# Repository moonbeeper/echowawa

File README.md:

# echowawa

> [!NOTE]
> This project is still in progress and not even close to being finished. Not even built yet.

Your typical DAC with bluetooth audio (with possible upgrades to use WiFi sources) and a USB C as an AUX port. It can output to either RCA jacks or a headphone jack. It also features a pretty fancy oled screen with its cool menu navigated via the knob.

The reason I made this was because of the fact that I am no longer a fan of using cheap bluetooth magic boxes with bad audio output when I can make my own magic box with probably better audio quality and a better design.

## Images

> The echowawa pcb

> The echowawa case

> The echowawa root schematic

> The echowawa power schematic

> The echowawa audio schematic

## BOM

> NOTE: This is a copy of the BOM.csv file. The shipping cost might be actually higher than the price listed here.

| Item | Quantity | LCSC Part Number | Cost EUR | Cost USD | Link |
|---|---|---|---|---|---|
| 1uF Capacitor | 26 | C29936 | 0,25 € | $0,28 | <https://lcsc.com/product-detail/Multilayer-Ceramic-Capacitors-MLCC-SMD-SMT_Samsung-Electro-Mechanics-CL10B105KA8NNNC_C29936.html> |
| 100nF Capacitor | 5 | C14663 | 0,22 € | $0,25 | <https://lcsc.com/product-detail/Multilayer-Ceramic-Capacitors-MLCC-SMD-SMT_YAGEO-CC0603KRX7R9BB104_C14663.html> |
| 10uF Electrolytic Capacitor | 4 | C22387953 | 0,21 € | $0,24 | <https://lcsc.com/product-detail/Aluminum-Electrolytic-Capacitors-SMD_FOLLON-EFVH025ADA100M0454_C22387953.html> |
| 2.2nF Capacitor | 4 | C107082 | 0,23 € | $0,26 | <https://lcsc.com/product-detail/Multilayer-Ceramic-Capacitors-MLCC-SMD-SMT_YAGEO-CC0603KRX7R9BB222_C107082.html> |
| 4.7uF Capacitor | 2 | C389010 | 0,30 € | $0,35 | <https://lcsc.com/product-detail/Multilayer-Ceramic-Capacitors-MLCC-SMD-SMT_muRata-GRM188Z71C475KE21D_C389010.html> |
| 27pF Capacitor | 2 | C376778 | 0,23 € | $0,26 | <https://lcsc.com/product-detail/Multilayer-Ceramic-Capacitors-MLCC-SMD-SMT_CCTC-TCC0603COG270J500CT_C376778.html> |
| 2.2uF Capacitor | 2 | C914769 | 0,43 € | $0,49 | <https://lcsc.com/product-detail/Multilayer-Ceramic-Capacitors-MLCC-SMD-SMT_YAGEO-CC0603KRX7R7BB225_C914769.html> |
| 100pF Capacitor | 2 | C14858 | 0,29 € | $0,33 | <https://lcsc.com/product-detail/Multilayer-Ceramic-Capacitors-MLCC-SMD-SMT_Samsung-Electro-Mechanics-CL10C101JB8NNNC_C14858.html> |
| 100uF Electrolytic Capacitor | 2 | C99837 | 0,28 € | $0,32 | <https://lcsc.com/product-detail/Aluminum-Electrolytic-Capacitors-SMD_ROQANG-RVE1V101M0607_C99837.html> |
| 3.3uF Capacitor | 1 | C5360803 | 0,55 € | $0,63 | <https://lcsc.com/product-detail/Multilayer-Ceramic-Capacitors-MLCC-SMD-SMT_CCTC-TCC0603X5R335M250CT_C5360803.html> |
| 5.1K Resistor | 4 | C105580 | 0,11 € | $0,12 | <https://lcsc.com/product-detail/Chip-Resistor-Surface-Mount_YAGEO-RC0603FR-075K1L_C105580.html> |
| 24K Resistor | 4 | C23352 | 0,10 € | $0,11 | <https://lcsc.com/product-detail/Chip-Resistor-Surface-Mount_UNI-ROYAL-0603WAF2402T5E_C23352.html> |
| 3.3K Resistor | 4 | C108078 | 0,11 € | $0,12 | <https://lcsc.com/product-detail/Chip-Resistor-Surface-Mount_YAGEO-RC0603FR-073K3L_C108078.html> |
| 4.7K Resistor | 3 | C99782 | 0,10 € | $0,11 | <https://lcsc.com/product-detail/Chip-Resistor-Surface-Mount_YAGEO-RC0603FR-074K7L_C99782.html> |
| 470 Resistor | 3 | C114669 | 0,11 € | $0,12 | <https://lcsc.com/product-detail/Chip-Resistor-Surface-Mount_YAGEO-RC0603FR-07470RL_C114669.html> |
| 0 Resistor | 1 | C95177  | 0,10 € | $0,11 | <https://lcsc.com/product-detail/Chip-Resistor-Surface-Mount_YAGEO-RC0603JR-070RL_C95177.html> |
| 10K Resistor | 1 | C98220 | 0,10 € | $0,11 | <https://lcsc.com/product-detail/Chip-Resistor-Surface-Mount_YAGEO-RC0603FR-0710KL_C98220.html> |
| 1.5K Resistor | 1 | C114668 | 0,11 € | $0,12 | <https://lcsc.com/product-detail/Chip-Resistor-Surface-Mount_YAGEO-RC0603FR-071K5L_C114668.html> |
| 1M Resistor | 1 | C105578 | 0,11 € | $0,12 | <https://lcsc.com/product-detail/Chip-Resistor-Surface-Mount_YAGEO-RC0603FR-071ML_C105578.html> |
| 100 Resistor | 1 | C105588 | 0,09 € | $0,10 | <https://lcsc.com/product-detail/Chip-Resistor-Surface-Mount_YAGEO-RC0603FR-07100RL_C105588.html> |
| 6.8uH Power Inductor | 1 | C135295 | 0,41 € | $0,47 | <https://lcsc.com/product-detail/Power-Inductors_SXN-Shun-Xiang-Nuo-Elec-SMNR6020-6R8MT_C135295.html> |
| Neopixel | 2 | C965555 | 0,36 € | $0,41 | <https://lcsc.com/product-detail/RGB-LEDs-Built-in-IC_Worldsemi-WS2812B-2020_C965555.html> |
| LED (Green) | 1 | C965804 | 0,39 € | $0,44 | <https://lcsc.com/product-detail/LED-Indication-Discrete_XINGLIGHT-XL-1608UGC-04_C965804.html> |
| XC6220B331MR | 2 | C86534 | 0,78 € | $0,89 | <https://lcsc.com/product-detail/Voltage-Regulators-Linear-Low-Drop-Out-LDO-Regulators_TOREX-XC6220B331MR-G_C86534.html> |
| TS5A22364DGSR | 2 | C105181 | 1,22 € | $1,40 | <https://lcsc.com/product-detail/Analog-Switches-Multiplexers_TI-TS5A22364DGSR_C105181.html> |
| ESP32-WROOM-32E-N8 | 1 | C701342 | 4,05 € | $4,65 | <https://lcsc.com/product-detail/WiFi-Modules_ESPRESSIF-ESP32-WROOM-32E-N8_C701342.html> |
| TLP185xSE | 1 | C7240 | 0,44 € | $0,51 | <https://lcsc.com/product-detail/Transistor-Photovoltaic-Output-Optoisolators_TOSHIBA-TLP185-GB-TPL-SE-T_C7240.html> |
| ADUM3160 | 1 | C284149 | 4,22 € | $4,85 | <https://lcsc.com/product-detail/Isolated-USB-ICs_ADI-ADUM3160BRWZ-RL_C284149.html> |
| F0505S-3WR2  | 1 | C5369564 | 1,93 € | $2,22 | <https://lcsc.com/product-detail/Isolated-Power-Modules_YLPTEC-F0505S-3WR2_C5369564.html> |
| PCM5100APWR | 1 | C131154 | 0,74 € | $0,85 | <https://lcsc.com/product-detail/ADCs-DACs-Special-Purpose_TI-PCM5100APWR_C131154.html> |
| PCM2912APJTR | 1 | C475497 | 3,80 € | $4,36 | <https://lcsc.com/product-detail/Audio-Interface-ICs_TI-PCM2912APJTR_C475497.html> |
| 6MHz Crystal | 1 | C7528811 | 0,39 € | $0,45 | <https://lcsc.com/product-detail/Crystals_YXC-Crystal-Oscillators-H6OEL89CSC-SUGYLC-6M_C7528811.html> |
| EC11E18244AU | 1 | C202365 | 1,71 € | $1,96 | <https://lcsc.com/product-detail/Rotary-Encoders_ALPSALPINE-EC11E18244AU_C202365.html> |
| Round TINY SMD Button | 2 | C720477 | 0,36 € | $0,41 | <https://lcsc.com/product-detail/Tactile-Switches_XUNPU-TS-1088-AR02016_C720477.html> |
| Audio Transformer | 2 | C596483 | 1,56 € | $1,79 | <https://lcsc.com/product-detail/Audio-Transformers_Sumida-ESMIT-4180-C_C596483.html> |
| RCA Jack | 2 | C18080 | 0,48 € | $0,55 | <https://lcsc.com/product-detail/RCA-Connector_BOOMELE-Boom-Precision-Elec-AV-5_C18080.html> |
| USBC Power Only | 1 | C668623 | 0,31 € | $0,35 | <https://lcsc.com/product-detail/USB-Connectors_SHOU-HAN-TYPE-C-6P-073_C668623.html> |
| USBC USB2.0 | 1 | C2988369 | 0,35 € | $0,40 | <https://lcsc.com/product-detail/USB-Connectors_G-Switch-GT-USB-7010ASV_C2988369.html> |
| Headphone Jack | 1 | C381131 | 0,46 € | $0,53 | <https://lcsc.com/product-detail/Audio-Connectors_XKB-Connection-PJ-3136-B_C381131.html> |
| 1.3 Inch OLED 128x64 | 1 | ----- | 2,80 € | $3,29 | <https://es.aliexpress.com/item/1005007451015054.html> |
| JLCPCB Echowawa 4 Layer PCB | 5 | ----- | 5,95 € | $7,00 | ----- |
| M2.5 Heat Inserts OD4mm Length 6mm  | 4 | ----- | 2,38 € | $2,79 | <https://es.aliexpress.com/item/1005003582355741.html> |
| M2.5 Allen Bolts 20mm Stainless Steel | 4 | ----- | 2,41 € | $2,83 | <https://es.aliexpress.com/item/32810872544.html> |
| USB to Serial Adapter | 1 |  | 1,41 € | $1,66 | <https://es.aliexpress.com/item/1005006445462581.html> |
| ~Shipping | ----- | ----- | 15 € | $17,61 | ----- |
| TOTAL | ----- | ----- | 57,94 € | $67,22 | ----- |

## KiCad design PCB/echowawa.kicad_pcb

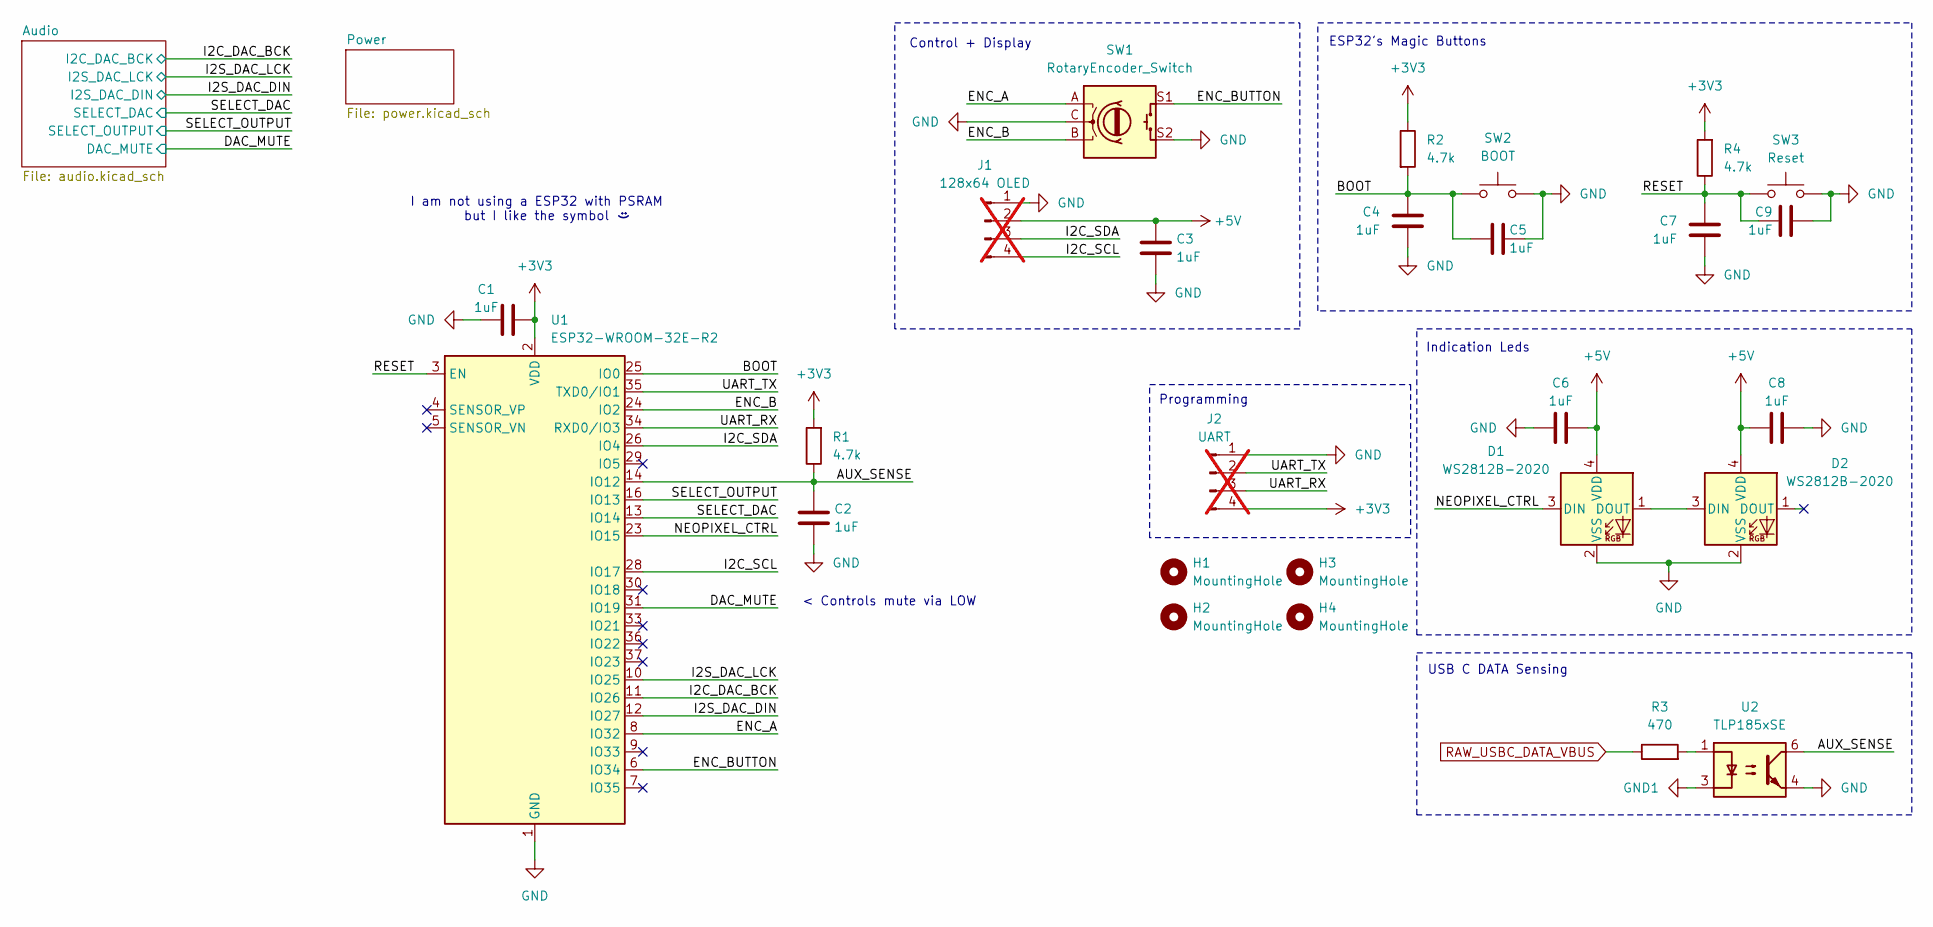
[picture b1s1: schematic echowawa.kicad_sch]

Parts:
C1, C2, C3, C4, C5, C6, C7, C8, C9: 1uF; C_0603_1608Metric_Pad1.08x0.95mm_HandSolder; LCSC C29936
D1, D2: WS2812B-2020; LED_WS2812B-2020_PLCC4_2.0x2.0mm; LCSC C965555
H1, H2, H3, H4: MountingHole; MountingHole_2.7mm_M2.5
J1: 128x64 OLED; PinHeader_1x04_P2.54mm_Vertical; not fitted
J2: UART; PinHeader_1x04_P2.54mm_Vertical; not fitted
R1, R2, R4: 4.7k; R_0603_1608Metric_Pad0.98x0.95mm_HandSolder; LCSC C99782
R3: 470; R_0603_1608Metric_Pad0.98x0.95mm_HandSolder; LCSC C114669
SW1: RotaryEncoder_Switch; RotaryEncoder_Alps_EC11E-Switch_Vertical_H20mm; LCSC C202365
SW2: BOOT; SW-SMD_L3.9-W3.0-P4.45; LCSC C720477
SW3: Reset; SW-SMD_L3.9-W3.0-P4.45; LCSC C720477
U1: ESP32-WROOM-32E-R2; ESP32-WROOM-32D; LCSC C701342
U2: TLP185xSE; SOIC-4_4.55x3.7mm_P2.54mm; LCSC C7240

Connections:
+3V3: C1.1, J2.4, R1.2, R2.1, R4.2, U1.2 (VDD); also elsewhere on the board
+5V: C3.2, C6.2, C8.1, D1.4 (VDD), D2.4 (VDD), J1.2; also elsewhere on the board
/AUX_SENSE: C2.2, R1.1, U1.14 (IO12), U2.6
/BOOT: C4.2, C5.1, R2.2, SW2.1, U1.25 (IO0); also elsewhere on the board
/DAC_MUTE: U1.31 (IO19); also elsewhere on the board
/ENC_A: SW1.A, U1.8 (IO32)
/ENC_B: SW1.B, U1.24 (IO2)
/ENC_BUTTON: SW1.S1, U1.6 (IO34)
/I2C_DAC_BCK: U1.11 (IO26); also elsewhere on the board
/I2C_SCL: J1.4, U1.28 (IO17)
/I2C_SDA: J1.3, U1.26 (IO4)
/I2S_DAC_DIN: U1.12 (IO27); also elsewhere on the board
/I2S_DAC_LCK: U1.10 (IO25); also elsewhere on the board
/NEOPIXEL_CTRL: D1.3 (DIN), U1.23 (IO15)
/RESET: C7.2, C9.1, R4.1, SW3.1, U1.3 (EN); also elsewhere on the board
/SELECT_DAC: U1.13 (IO14); also elsewhere on the board
/SELECT_OUTPUT: U1.16 (IO13); also elsewhere on the board
/UART_RX: J2.3, U1.34 (RXD0/IO3)
/UART_TX: J2.2, U1.35 (TXD0/IO1)
GND: C1.2, C2.1, C3.1, C4.1, C5.2, C6.1, C7.1, C8.2, C9.2, D1.2 (VSS), D2.2 (VSS), J1.1, J2.1, SW1.C, SW1.S2, SW2.2, SW3.2, U1.1 (GND), U1.15 (GND), U1.38 (GND), U1.39 (GND), U2.4; also elsewhere on the board
GND1: U2.3; also elsewhere on the board
unnamed: D1.1 (DOUT), D2.3 (DIN)
unnamed: R3.2, U2.1
RAW_USBC_DATA_VBUS: R3.1; also elsewhere on the board

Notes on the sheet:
ESP32's Magic Buttons
Programming
Indication Leds
< Controls mute via LOW
USB C DATA Sensing
Control + Display
I am not using a ESP32 with PSRAM but I like the symbol

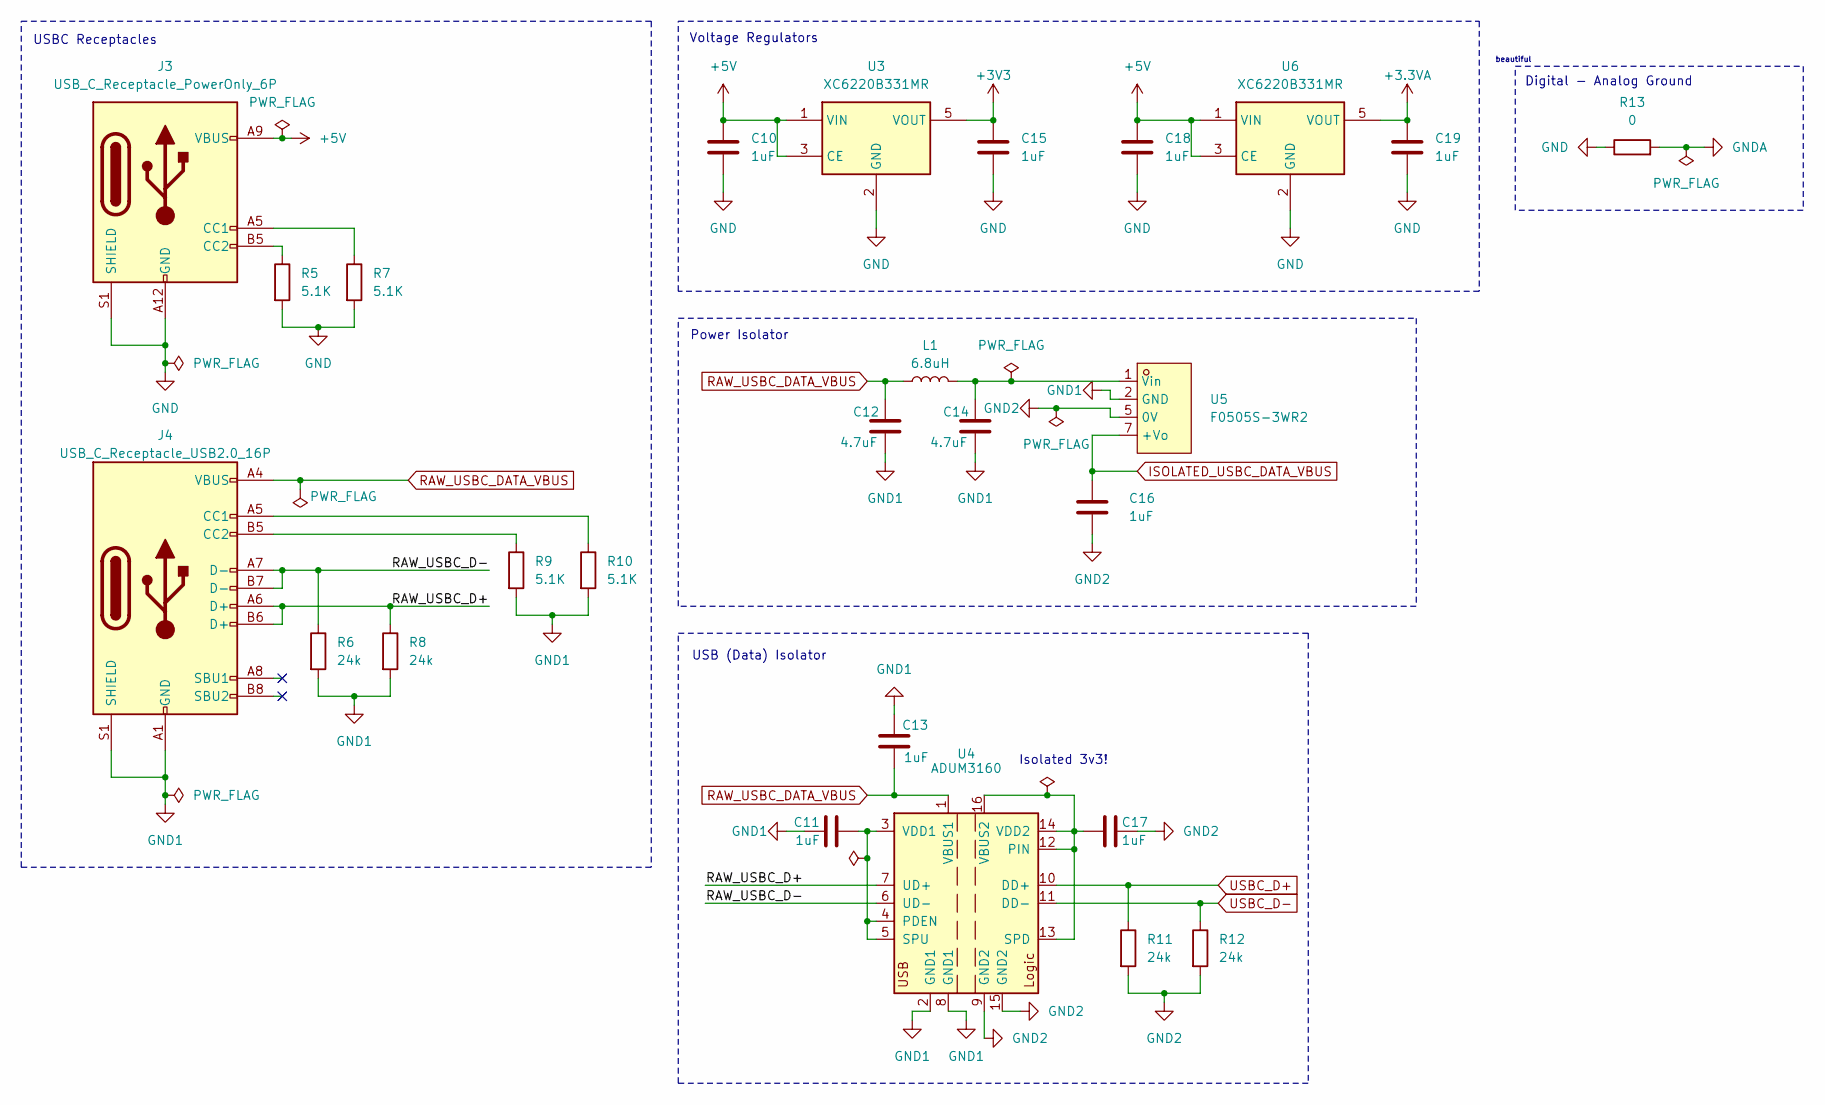
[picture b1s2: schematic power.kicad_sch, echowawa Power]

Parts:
C10, C11, C13, C15, C16, C17, C18, C19: 1uF; C_0603_1608Metric_Pad1.08x0.95mm_HandSolder; LCSC C29936
C12, C14: 4.7uF; C_0603_1608Metric_Pad1.08x0.95mm_HandSolder; LCSC C389010
J3: USB_C_Receptacle_PowerOnly_6P; TYPE-C-SMD_TYPE-C-6P-073; LCSC C668623
J4: USB_C_Receptacle_USB2.0_16P; USB_C_Receptacle_G-Switch_GT-USB-7010ASV; LCSC C2988369
L1: 6.8uH; L_6.3x6.3_H3; LCSC C135295
R5, R7, R9, R10: 5.1K; R_0603_1608Metric_Pad0.98x0.95mm_HandSolder; LCSC C105580
R6, R8, R11, R12: 24k; R_0603_1608Metric_Pad0.98x0.95mm_HandSolder; LCSC C23352
R13: 0; R_0603_1608Metric_Pad0.98x0.95mm_HandSolder; LCSC C95177
U3, U6: XC6220B331MR; SOT-23-5; LCSC C86534
U4: ADUM3160; SOIC-16W_7.5x10.3mm_P1.27mm; LCSC C284149
U5: F0505S-3WR2; PWRM-TH_4P-L19.7-W6.0-P2.54_F2403S-1WR3; LCSC C5369564

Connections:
+3.3VA: C19.1, U6.5 (VOUT); also elsewhere on the board
+3V3: C15.1, U3.5 (VOUT); also elsewhere on the board
+5V: C10.1, C18.1, J3.A9 (VBUS), J3.B9 (VBUS), U3.1 (VIN), U3.3 (CE), U6.1 (VIN), U6.3 (CE); also elsewhere on the board
/Power/RAW_USBC_D+: J4.A6 (D+), J4.B6 (D+), R8.1, U4.7 (UD+)
/Power/RAW_USBC_D-: J4.A7 (D-), J4.B7 (D-), R6.1, U4.6 (UD-)
GND: C10.2, C15.2, C18.2, C19.2, J3.A12 (GND), J3.B12 (GND), J3.S1 (SHIELD), R5.2, R7.2, R13.1, U3.2 (GND), U6.2 (GND); also elsewhere on the board
GND1: C11.1, C12.1, C13.1, C14.1, J4.A1 (GND), J4.A12 (GND), J4.B1 (GND), J4.B12 (GND), J4.S1 (SHIELD), R6.2, R8.2, R9.2, R10.2, U4.2 (GND1), U4.8 (GND1), U5.2 (GND); also elsewhere on the board
GND2: C16.2, C17.1, R11.2, R12.2, U4.9 (GND2), U4.15 (GND2), U5.5 (0V); also elsewhere on the board
GNDA: R13.2; also elsewhere on the board
ISOLATED_USBC_DATA_VBUS: C16.1, U5.7 (+Vo); also elsewhere on the board
unnamed: J3.A5 (CC1), R7.1
unnamed: J3.B5 (CC2), R5.1
unnamed: J4.A5 (CC1), R10.1
unnamed: J4.B5 (CC2), R9.1
unnamed: C11.2, U4.3 (VDD1), U4.4 (PDEN), U4.5 (SPU)
unnamed: C17.2, U4.12 (PIN), U4.13 (SPD), U4.14 (VDD2), U4.16 (VBUS2)
unnamed: C14.2, L1.2, U5.1 (Vin)
RAW_USBC_DATA_VBUS: C12.2, C13.2, J4.A4 (VBUS), J4.A9 (VBUS), J4.B4 (VBUS), J4.B9 (VBUS), L1.1, U4.1 (VBUS1); also elsewhere on the board
USBC_D+: R11.1, U4.10 (DD+); also elsewhere on the board
USBC_D-: R12.1, U4.11 (DD-); also elsewhere on the board

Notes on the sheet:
Power Isolator
USBC Receptacles
beautiful
Voltage Regulators
Isolated 3v3!
USB (Data) Isolator
Digital - Analog Ground

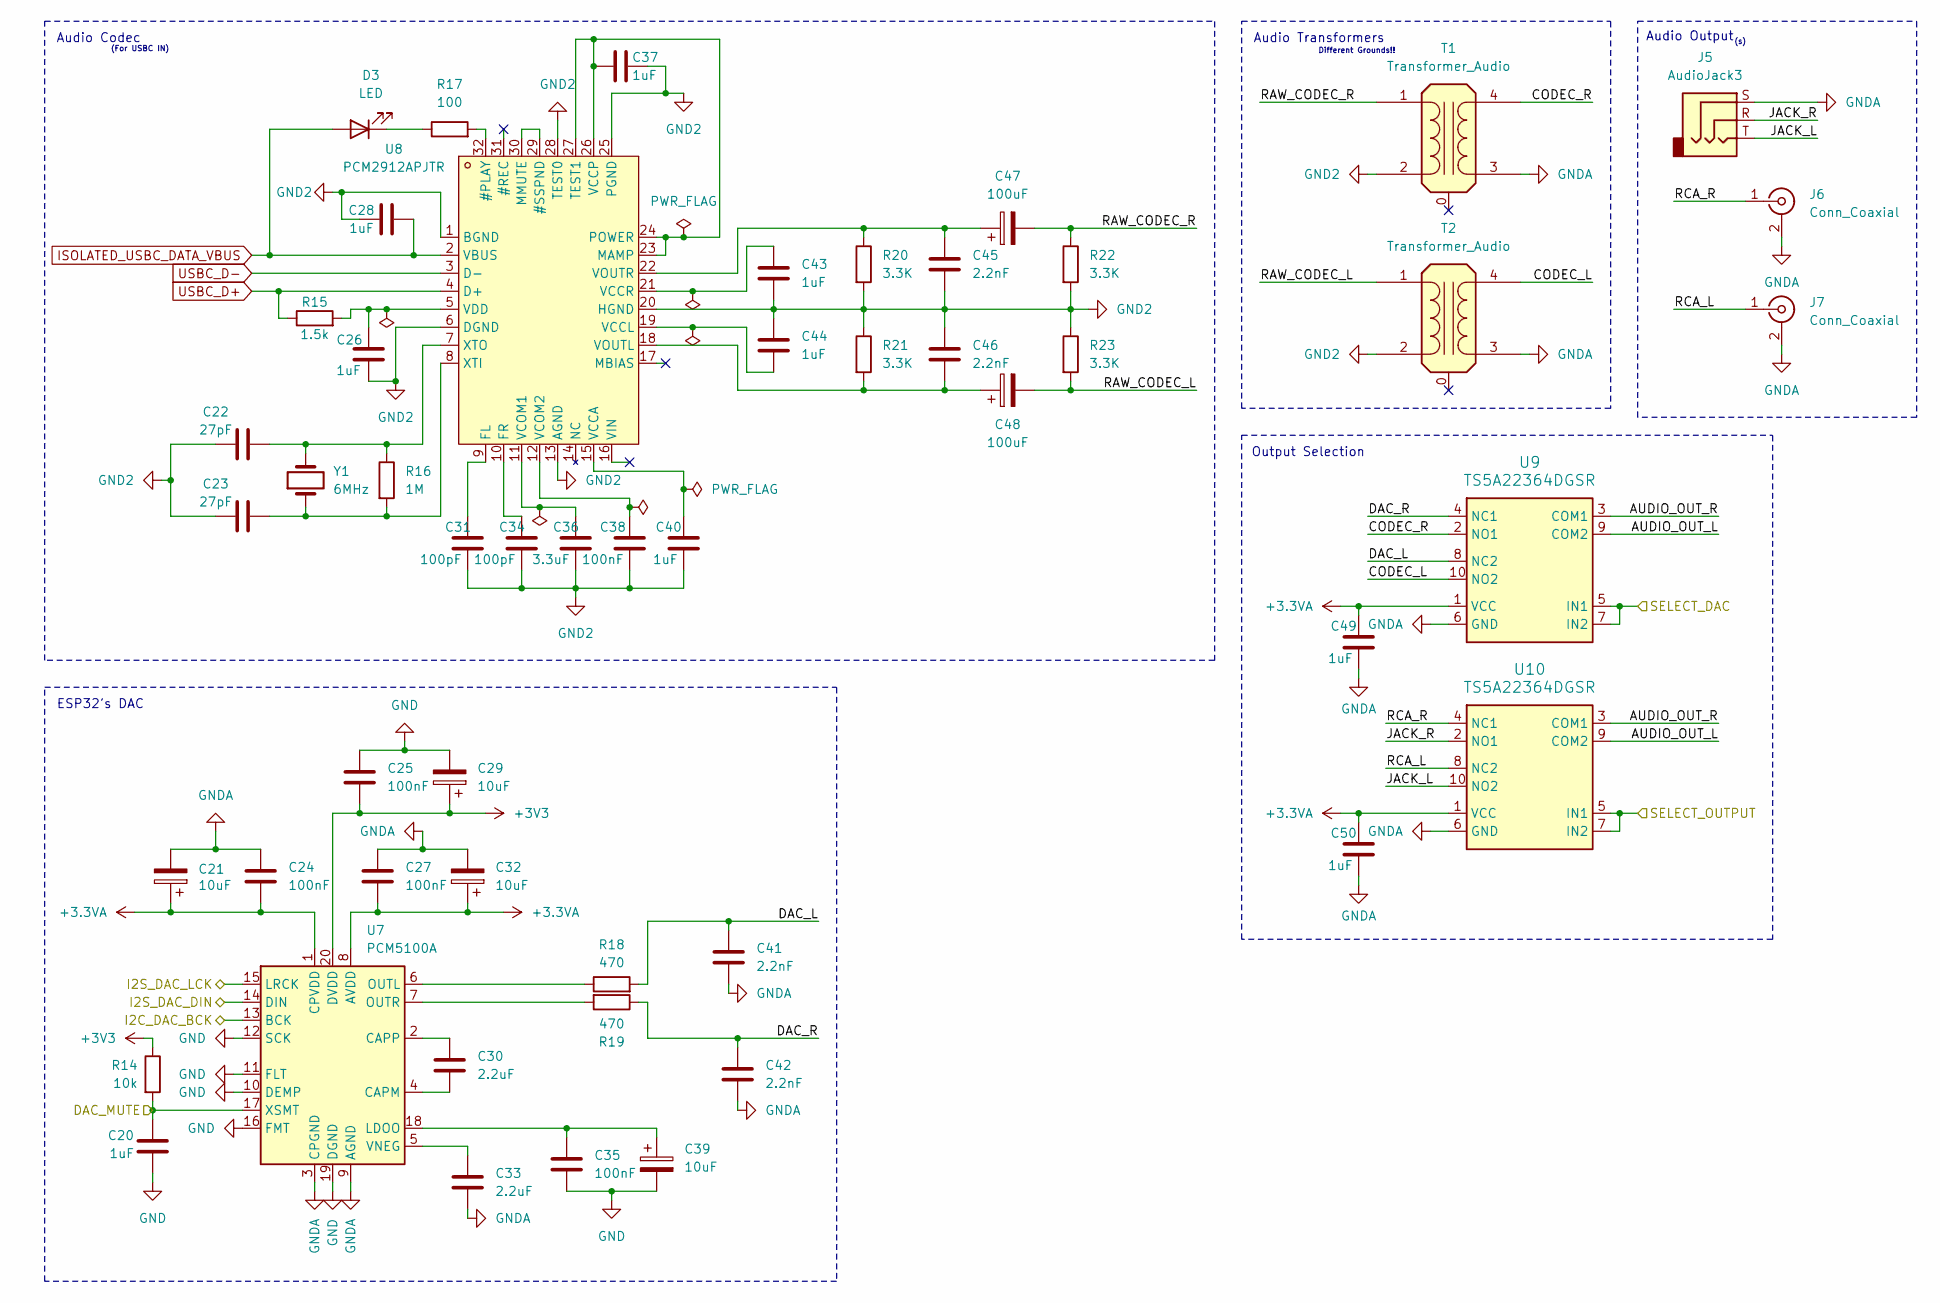
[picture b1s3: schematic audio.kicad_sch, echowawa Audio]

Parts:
C20, C26, C28, C37, C40, C43, C44, C49, C50: 1uF; C_0603_1608Metric_Pad1.08x0.95mm_HandSolder; LCSC C29936
C21, C29, C32, C39: 10uF; CP_Elec_4x5.4; LCSC C22387953
C22, C23: 27pF; C_0603_1608Metric_Pad1.08x0.95mm_HandSolder; LCSC C376778
C24, C25, C27, C35, C38: 100nF; C_0603_1608Metric_Pad1.08x0.95mm_HandSolder; LCSC C14663
C30, C33: 2.2uF; C_0603_1608Metric_Pad1.08x0.95mm_HandSolder; LCSC C914769
C31, C34: 100pF; C_0603_1608Metric_Pad1.08x0.95mm_HandSolder; LCSC C14858
C36: 3.3uF; C_0603_1608Metric_Pad1.08x0.95mm_HandSolder; LCSC C5360803
C41, C42, C45, C46: 2.2nF; C_0603_1608Metric_Pad1.08x0.95mm_HandSolder; LCSC C107082
C47, C48: 100uF; CP_Elec_6.3x7.7; LCSC C99837
D3: LED; LED_0603_1608Metric_Pad1.05x0.95mm_HandSolder; LCSC C965804
J5: AudioJack3; AUDIO-TH_PJ-3136-B; LCSC C381131
J6, J7: Conn_Coaxial; CONN-TH_AV-5; LCSC C18080
R14: 10k; R_0603_1608Metric_Pad0.98x0.95mm_HandSolder; LCSC C98220
R15: 1.5k; R_0603_1608Metric_Pad0.98x0.95mm_HandSolder; LCSC C114668
R16: 1M; R_0603_1608Metric_Pad0.98x0.95mm_HandSolder; LCSC C105578
R17: 100; R_0603_1608Metric_Pad0.98x0.95mm_HandSolder; LCSC C105588
R18, R19: 470; R_0603_1608Metric_Pad0.98x0.95mm_HandSolder; LCSC C114669
R20, R21, R22, R23: 3.3K; R_0603_1608Metric_Pad0.98x0.95mm_HandSolder; LCSC C108078
T1, T2: Transformer_Audio; XFMR-SMD_4P-L7.1-W5.2-P2.54-LS9.2-BL; LCSC C596483
U7: PCM5100A; TSSOP-20_4.4x6.5mm_P0.65mm; LCSC C131154
U8: PCM2912APJTR; TQFP-32_7x7mm_P0.8mm; LCSC C475497
U9, U10: TS5A22364DGSR; VSSOP-10_3x3mm_P0.5mm; LCSC C105181
Y1: 6MHz; Crystal_SMD_HC49-SD_HandSoldering; LCSC C7528811

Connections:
+3.3VA: C21.1, C24.2, C27.2, C32.1, C49.2, C50.2, U7.1 (CPVDD), U7.8 (AVDD), U9.1 (VCC), U10.1 (VCC); also elsewhere on the board
+3V3: C25.2, C29.1, R14.1, U7.20 (DVDD); also elsewhere on the board
/Audio/AUDIO_OUT_L: U9.9 (COM2), U10.9 (COM2)
/Audio/AUDIO_OUT_R: U9.3 (COM1), U10.3 (COM1)
/Audio/CODEC_L: T2.4 (SB), U9.10 (NO2)
/Audio/CODEC_R: T1.4 (SB), U9.2 (NO1)
/Audio/DAC_L: C41.1, R18.2, U9.8 (NC2)
/Audio/DAC_R: C42.1, R19.1, U9.4 (NC1)
/Audio/JACK_L: J5.T, U10.10 (NO2)
/Audio/JACK_R: J5.R, U10.2 (NO1)
/Audio/RAW_CODEC_L: C48.2, R23.2, T2.1 (AA)
/Audio/RAW_CODEC_R: C47.2, R22.1, T1.1 (AA)
/Audio/RCA_L: J7.1 (In), U10.8 (NC2)
/Audio/RCA_R: J6.1 (In), U10.4 (NC1)
/DAC_MUTE: C20.1, R14.2, U7.17 (XSMT); also elsewhere on the board
/I2C_DAC_BCK: U7.13 (BCK); also elsewhere on the board
/I2S_DAC_DIN: U7.14 (DIN); also elsewhere on the board
/I2S_DAC_LCK: U7.15 (LRCK); also elsewhere on the board
/SELECT_DAC: U9.5 (IN1), U9.7 (IN2); also elsewhere on the board
/SELECT_OUTPUT: U10.5 (IN1), U10.7 (IN2); also elsewhere on the board
GND: C20.2, C25.1, C29.2, C35.2, C39.2, U7.10 (DEMP), U7.11 (FLT), U7.12 (SCK), U7.16 (FMT), U7.19 (DGND); also elsewhere on the board
GND2: C22.1, C23.1, C26.1, C28.1, C31.1, C34.1, C36.1, C37.2, C38.1, C40.1, C43.1, C44.1, C45.2, C46.1, R20.2, R21.1, R22.2, R23.1, T1.2 (AB), T2.2 (AB), U8.1 (BGND), U8.6 (DGND), U8.13 (AGND), U8.20 (HGND), U8.25 (PGND), U8.28 (TEST0); also elsewhere on the board
GNDA: C21.2, C24.1, C27.1, C32.2, C33.2, C41.2, C42.2, C49.1, C50.1, J5.S, J6.2 (Ext), J7.2 (Ext), T1.3 (SA), T2.3 (SA), U7.3 (CPGND), U7.9 (AGND), U9.6 (GND), U10.6 (GND); also elsewhere on the board
ISOLATED_USBC_DATA_VBUS: C28.2, D3.2 (A), U8.2 (VBUS); also elsewhere on the board
unnamed: D3.1 (K), R17.1
unnamed: C30.2, U7.4 (CAPM)
unnamed: C30.1, U7.2 (CAPP)
unnamed: C35.1, C39.1, U7.18 (LDOO)
unnamed: R18.1, U7.6 (OUTL)
unnamed: R19.2, U7.7 (OUTR)
unnamed: C33.1, U7.5 (VNEG)
unnamed: R17.2, U8.32 (#PLAY)
unnamed: U8.29 (#SSPND), U8.30 (MMUTE)
unnamed: C31.2, U8.9 (FL)
unnamed: C34.2, U8.10 (FR)
unnamed: C37.1, U8.23 (MAMP), U8.24 (POWER), U8.26 (VCCP), U8.27 (TEST1)
unnamed: C40.2, U8.15 (VCCA)
unnamed: C44.2, U8.19 (VCCL)
unnamed: C43.2, U8.21 (VCCR)
unnamed: C36.2, U8.11 (VCOM1)
unnamed: C38.2, U8.12 (VCOM2)
unnamed: C26.2, R15.2, U8.5 (VDD)
unnamed: C46.2, C48.1, R21.2, U8.18 (VOUTL)
unnamed: C45.1, C47.1, R20.1, U8.22 (VOUTR)
unnamed: C23.2, R16.2, U8.8 (XTI), Y1.1
unnamed: C22.2, R16.1, U8.7 (XTO), Y1.2
USBC_D+: R15.1, U8.4 (D+); also elsewhere on the board
USBC_D-: U8.3 (D-); also elsewhere on the board

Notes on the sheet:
Output Selection
Audio Codec
ESP32's DAC
Audio Transformers
(s)
Different Grounds!!
(For USBC IN)
Audio Output

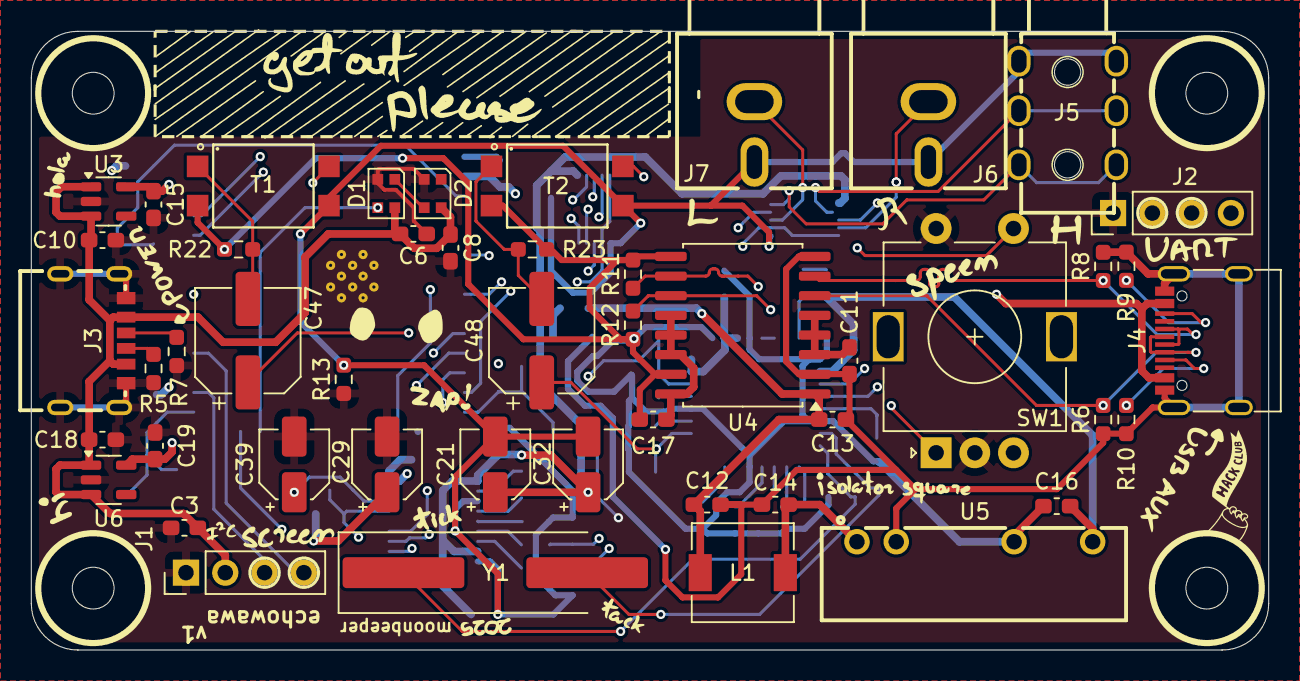
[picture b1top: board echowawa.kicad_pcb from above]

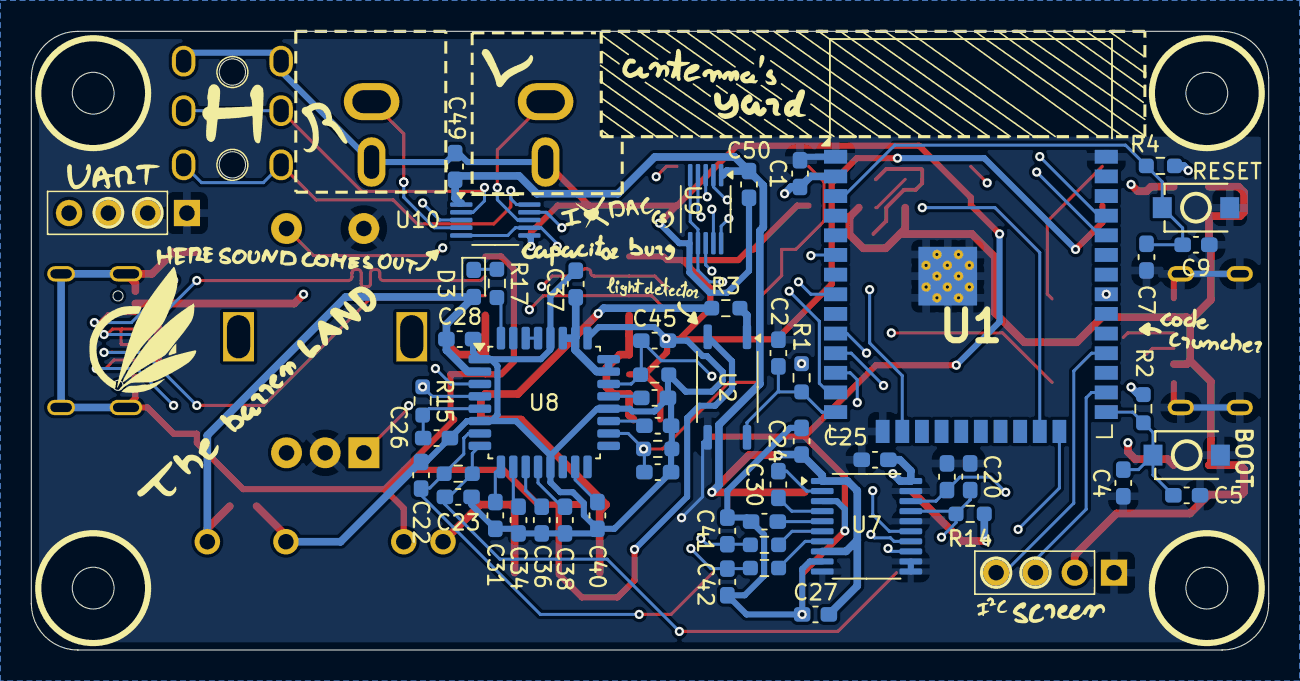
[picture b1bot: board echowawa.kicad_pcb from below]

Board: 4 copper layers, 80.0 x 40.0 mm, 104 parts (52 on the bottom side), 73 nets.

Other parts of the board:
BOOT: BOOT; SW-SMD_L3.9-W3.0-P4.45
RESET: Reset; SW-SMD_L3.9-W3.0-P4.45

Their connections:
/BOOT: BOOT.1; also elsewhere on the board
/RESET: RESET.1; also elsewhere on the board
GND: BOOT.2, RESET.2; also elsewhere on the board

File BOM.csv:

Item;Quantity;LCSC Part Number;Cost EUR;Cost USD;Link
1uF Capacitor;26;C29936;0,25 €; $0,28 ;https://lcsc.com/product-detail/Multilayer-Ceramic-Capacitor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
100nF Capacitor;5;C14663;0,22 €; $0,25 ;https://lcsc.com/product-detail/Multilayer-Ceramic-Capacitor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
10uF Electrolytic Capacitor;4;C22387953;0,21 €; $0,24 ;https://lcsc.com/product-detail/Aluminum-Electrolytic-Capaci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
2.2nF Capacitor;4;C107082;0,23 €; $0,26 ;https://lcsc.com/product-detail/Multilayer-Ceramic-Capacitor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
4.7uF Capacitor;2;C389010;0,30 €; $0,35 ;https://lcsc.com/product-detail/Multilayer-Ceramic-Capacitor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
27pF Capacitor;2;C376778;0,23 €; $0,26 ;https://lcsc.com/product-detail/Multilayer-Ceramic-Capacitor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
2.2uF Capacitor;2;C914769;0,43 €; $0,49 ;https://lcsc.com/product-detail/Multilayer-Ceramic-Capacitor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
100pF Capacitor;2;C14858;0,29 €; $0,33 ;https://lcsc.com/product-detail/Multilayer-Ceramic-Capacitor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
100uF Electrolytic Capacitor;2;C99837;0,28 €; $0,32 ;https://lcsc.com/product-detail/Aluminum-Electrolytic-Capaci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
3.3uF Capacitor;1;C5360803;0,55 €; $0,63 ;https://lcsc.com/product-detail/Multilayer-Ceramic-Capacitor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
5.1K Resistor;4;C105580;0,11 €; $0,12 ;https://lcsc.com/product-detail/Chip-Resistor-Surface-Mount_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
24K Resistor;4;C23352;0,10 €; $0,11 ;https://lcsc.com/product-detail/Chip-Resistor-Surface-Mount_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
3.3K Resistor;4;C108078;0,11 €; $0,12 ;https://lcsc.com/product-detail/Chip-Resistor-Surface-Mount_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
4.7K Resistor;3;C99782;0,10 €; $0,11 ;https://lcsc.com/product-detail/Chip-Resistor-Surface-Mount_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
470 Resistor;3;C114669;0,11 €; $0,12 ;https://lcsc.com/product-detail/Chip-Resistor-Surface-Mount_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
0 Resistor;1;"C95177	";0,10 €; $0,11 ;https://lcsc.com/product-detail/Chip-Resistor-Surface-Mount_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
10K Resistor;1;C98220;0,10 €; $0,11 ;https://lcsc.com/product-detail/Chip-Resistor-Surface-Mount_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
1.5K Resistor;1;C114668;0,11 €; $0,12 ;https://lcsc.com/product-detail/Chip-Resistor-Surface-Mount_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
1M Resistor;1;C105578;0,11 €; $0,12 ;https://lcsc.com/product-detail/Chip-Resistor-Surface-Mount_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
100 Resistor;1;C105588;0,09 €; $0,10 ;https://lcsc.com/product-detail/Chip-Resistor-Surface-Mount_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
6.8uH Power Inductor;1;C135295;0,41 €; $0,47 ;https://lcsc.com/product-detail/Power-Inductors_SXN-Shun-Xia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
Neopixel;2;C965555;0,36 €; $0,41 ;https://lcsc.com/product-detail/RGB-LEDs-Built-in-IC_Worldse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
LED (Green);1;C965804;0,39 €; $0,44 ;https://lcsc.com/product-detail/LED-Indication-Discrete_XING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
XC6220B331MR;2;C86534;0,78 €; $0,89 ;https://lcsc.com/product-detail/Voltage-Regulators-Linear-Lo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
TS5A22364DGSR;2;C105181;1,22 €; $1,40 ;https://lcsc.com/product-detail/Analog-Switches-Multiplexers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
ESP32-WROOM-32E-N8;1;C701342;4,05 €; $4,65 ;https://lcsc.com/product-detail/WiFi-Modules_ESPRESSIF-ESP32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
TLP185xSE;1;C7240;0,44 €; $0,51 ;https://lcsc.com/product-detail/Transistor-Photovoltaic-Outp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
ADUM3160;1;C284149;4,22 €; $4,85 ;https://lcsc.com/product-detail/Isolated-USB-ICs_ADI-ADUM316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
"F0505S-3WR2	";1;C5369564;1,93 €; $2,22 ;https://lcsc.com/product-detail/Isolated-Power-Modules_YLPTE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
PCM5100APWR;1;C131154;0,74 €; $0,85 ;https://lcsc.com/product-detail/ADCs-DACs-Special-Purpose_TI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
PCM2912APJTR;1;C475497;3,80 €; $4,36 ;https://lcsc.com/product-detail/Audio-Interface-ICs_TI-PCM29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
6MHz Crystal;1;C7528811;0,39 €; $0,45 ;https://lcsc.com/product-detail/Crystals_YXC-Crystal-Oscilla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
EC11E18244AU;1;C202365;1,71 €; $1,96 ;https://lcsc.com/product-detail/Rotary-Encoders_ALPSALPINE-E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
Round TINY SMD Button;2;C720477;0,36 €; $0,41 ;https://lcsc.com/product-detail/Tactile-Switches_XUNPU-TS-10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
Audio Transformer;2;C596483;1,56 €; $1,79 ;https://lcsc.com/product-detail/Audio-Transformers_Sumida-ES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
RCA Jack;2;C18080;0,48 €; $0,55 ;https://lcsc.com/product-detail/RCA-Connector_BOOMELE-Boom-P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
USBC Power Only;1;C668623;0,31 €; $0,35 ;https://lcsc.com/product-detail/USB-Connectors_SHOU-HAN-TYPE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
USBC USB2.0;1;C2988369;0,35 €; $0,40 ;https://lcsc.com/product-detail/USB-Connectors_G-Switch-GT-U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
Headphone Jack;1;C381131;0,46 €; $0,53 ;https://lcsc.com/product-detail/Audio-Connectors_XKB-Connect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
1.3 Inch OLED 128x64;1;-----;2,80 €; $3,29 ;https://es.aliexpress.com/item/1005007451015054.html
JLCPCB Echowawa 4 Layer PCB;5;-----;5,95 €; $7,00 ;-----
"M2.5 Heat Inserts OD4mm Length 6mm	";4;-----;2,38 €; $2,79 ;https://es.aliexpress.com/item/1005003582355741.html
M2.5 Allen Bolts 20mm Stainless Steel;4;-----;2,41 €; $2,83 ;https://es.aliexpress.com/item/32810872544.html
USB to Serial Adapter;1;;1,41 €; $1,66 ;https://es.aliexpress.com/item/1005006445462581.html
~Shipping;-----;-----;15 €; $17,61 ;-----
TOTAL;-----;-----;57,94 €; $67,22 ;-----

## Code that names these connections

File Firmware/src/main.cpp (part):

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
#define NEOPIXEL_CTRL 15
#define NEOPIXEL_COUNT 2
Adafruit_NeoPixel neo_strip(NEOPIXEL_COUNT, NEOPIXEL_CTRL, NEO_GRB + NEO_KHZ800);
void updateNeoStrip();

#define AUX_SENSE 12
#define SWAP_DAC 14
#define SWAP_OUTPUT 13

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bool currentDac = false;    // false = little one's DAC, true = Audio Codec
bool currentOutput = false; // false = headphone jack, true = RCA jacks

#define DAC_MUTE 19
#define DAC_DATA 27
#define DAC_BCK 26
#define DAC_LCK 25
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
void setup()
{
  pinMode(AUX_SENSE, INPUT);
  pinMode(SWAP_DAC, INPUT);
  pinMode(SWAP_OUTPUT, INPUT);
  pinMode(DAC_MUTE, OUTPUT);
  digitalWrite(DAC_MUTE, LOW);    // mute little one's dac
  digitalWrite(SWAP_DAC, LOW);    // default to little one's DAC
  digitalWrite(SWAP_OUTPUT, LOW); // default to headphone jack
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
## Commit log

2025-07-28 second commit
